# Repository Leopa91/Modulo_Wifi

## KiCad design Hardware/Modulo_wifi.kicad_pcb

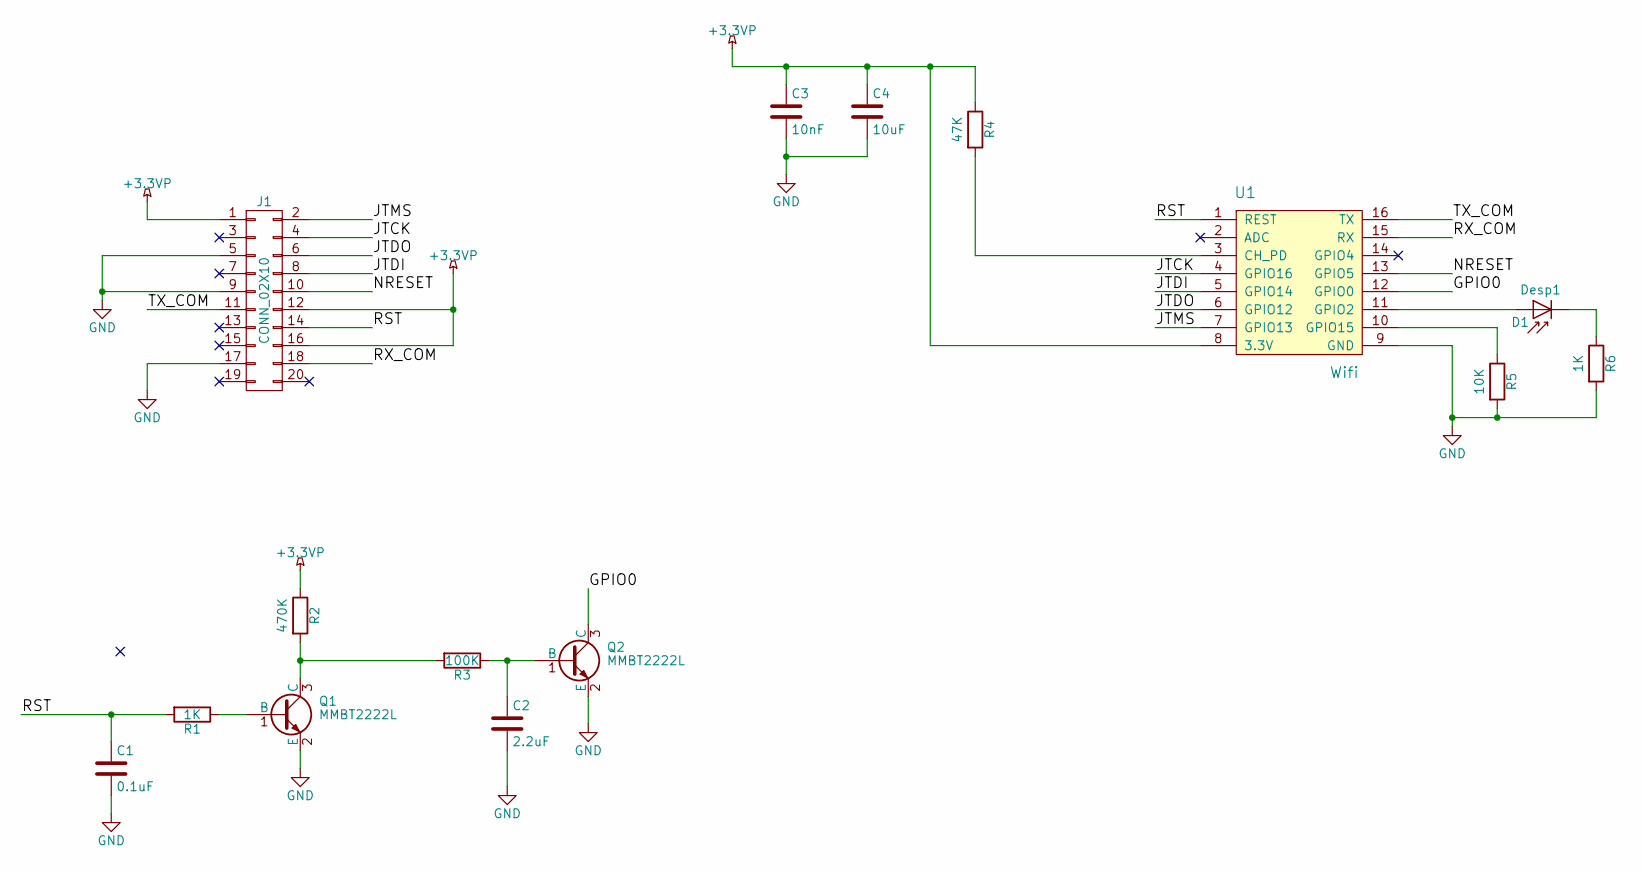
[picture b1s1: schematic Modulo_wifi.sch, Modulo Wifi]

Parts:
C1: 0.1uF; C_0603_HandSoldering
C2: 2.2uF; C_0603_HandSoldering
C3: 10nF; C_0603_HandSoldering
C4: 10uF; C_0603_HandSoldering
D1: Desp1; LED_0805
J1: CONN_02X10; IDC_Header_Straight_20pins
Q1, Q2: MMBT2222L; SOT-23_Handsoldering
R1, R6: 1K; R_0603_HandSoldering
R2: 470K; R_0603_HandSoldering
R3: 100K; R_0603_HandSoldering
R4: 47K; R_0603_HandSoldering
R5: 10K; R_0603_HandSoldering
U1: Wifi

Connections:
+3.3VP: C3.1, C4.1, J1.1, J1.12, J1.16, R2.1, R4.1, U1.8 (3.3V)
/GPIO0: Q2.3 (C), U1.12 (GPIO0)
/JTCK: J1.4, U1.4 (GPIO16)
/JTDI: J1.8, U1.5 (GPIO14)
/JTDO: J1.6, U1.6 (GPIO12)
/JTMS: J1.2, U1.7 (GPIO13)
/NRESET: J1.10, U1.13 (GPIO5)
/RST: C1.1, J1.14, R1.2, U1.1 (REST)
/RX_COM: J1.18, U1.15 (RX)
/TX_COM: J1.11, U1.16 (TX)
GND: C1.2, C2.2, C3.2, C4.2, J1.5, J1.9, J1.17, Q1.2 (E), Q2.2 (E), R5.2, R6.2, U1.9 (GND)
unnamed: C2.1, Q2.1 (B), R3.1
unnamed: D1.1 (K), R6.1
unnamed: D1.2 (A), U1.11 (GPIO2)
unnamed: Q1.1 (B), R1.1
unnamed: Q1.3 (C), R2.2, R3.2
unnamed: R4.2, U1.3 (CH_PD)
unnamed: R5.1, U1.10 (GPIO15)

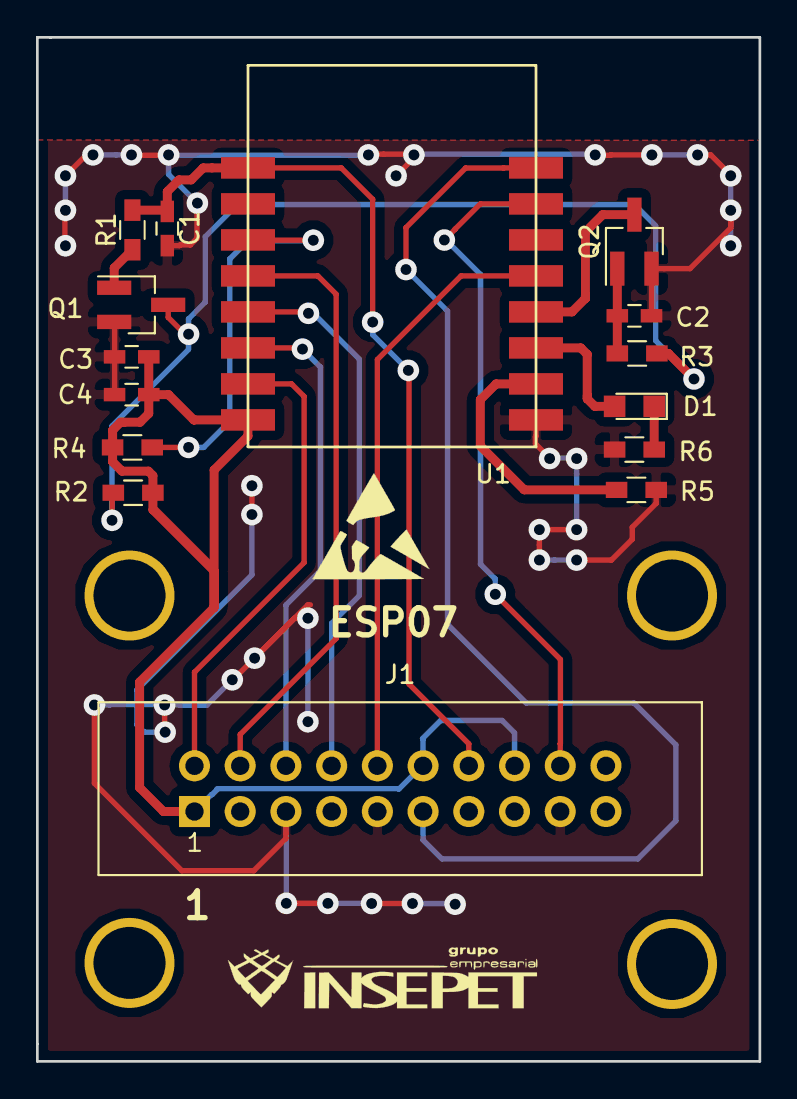
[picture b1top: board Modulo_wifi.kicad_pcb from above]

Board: 2 copper layers, 40.1 x 56.9 mm, 15 parts (0 on the bottom side), 18 nets.
